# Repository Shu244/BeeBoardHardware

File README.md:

# Overview

This repo contains a generic power supply for ESP32 and other MCUs. This board includes: 

1) Charging circuit with power path
2) Smart power button (for manually/programmtically controlling power)
3) Battery status  

The purpose of this board is to make an MCU portable with precise battery control and monitoring.

## Block Diagram

## Schematic

## PCB

## 3D Models

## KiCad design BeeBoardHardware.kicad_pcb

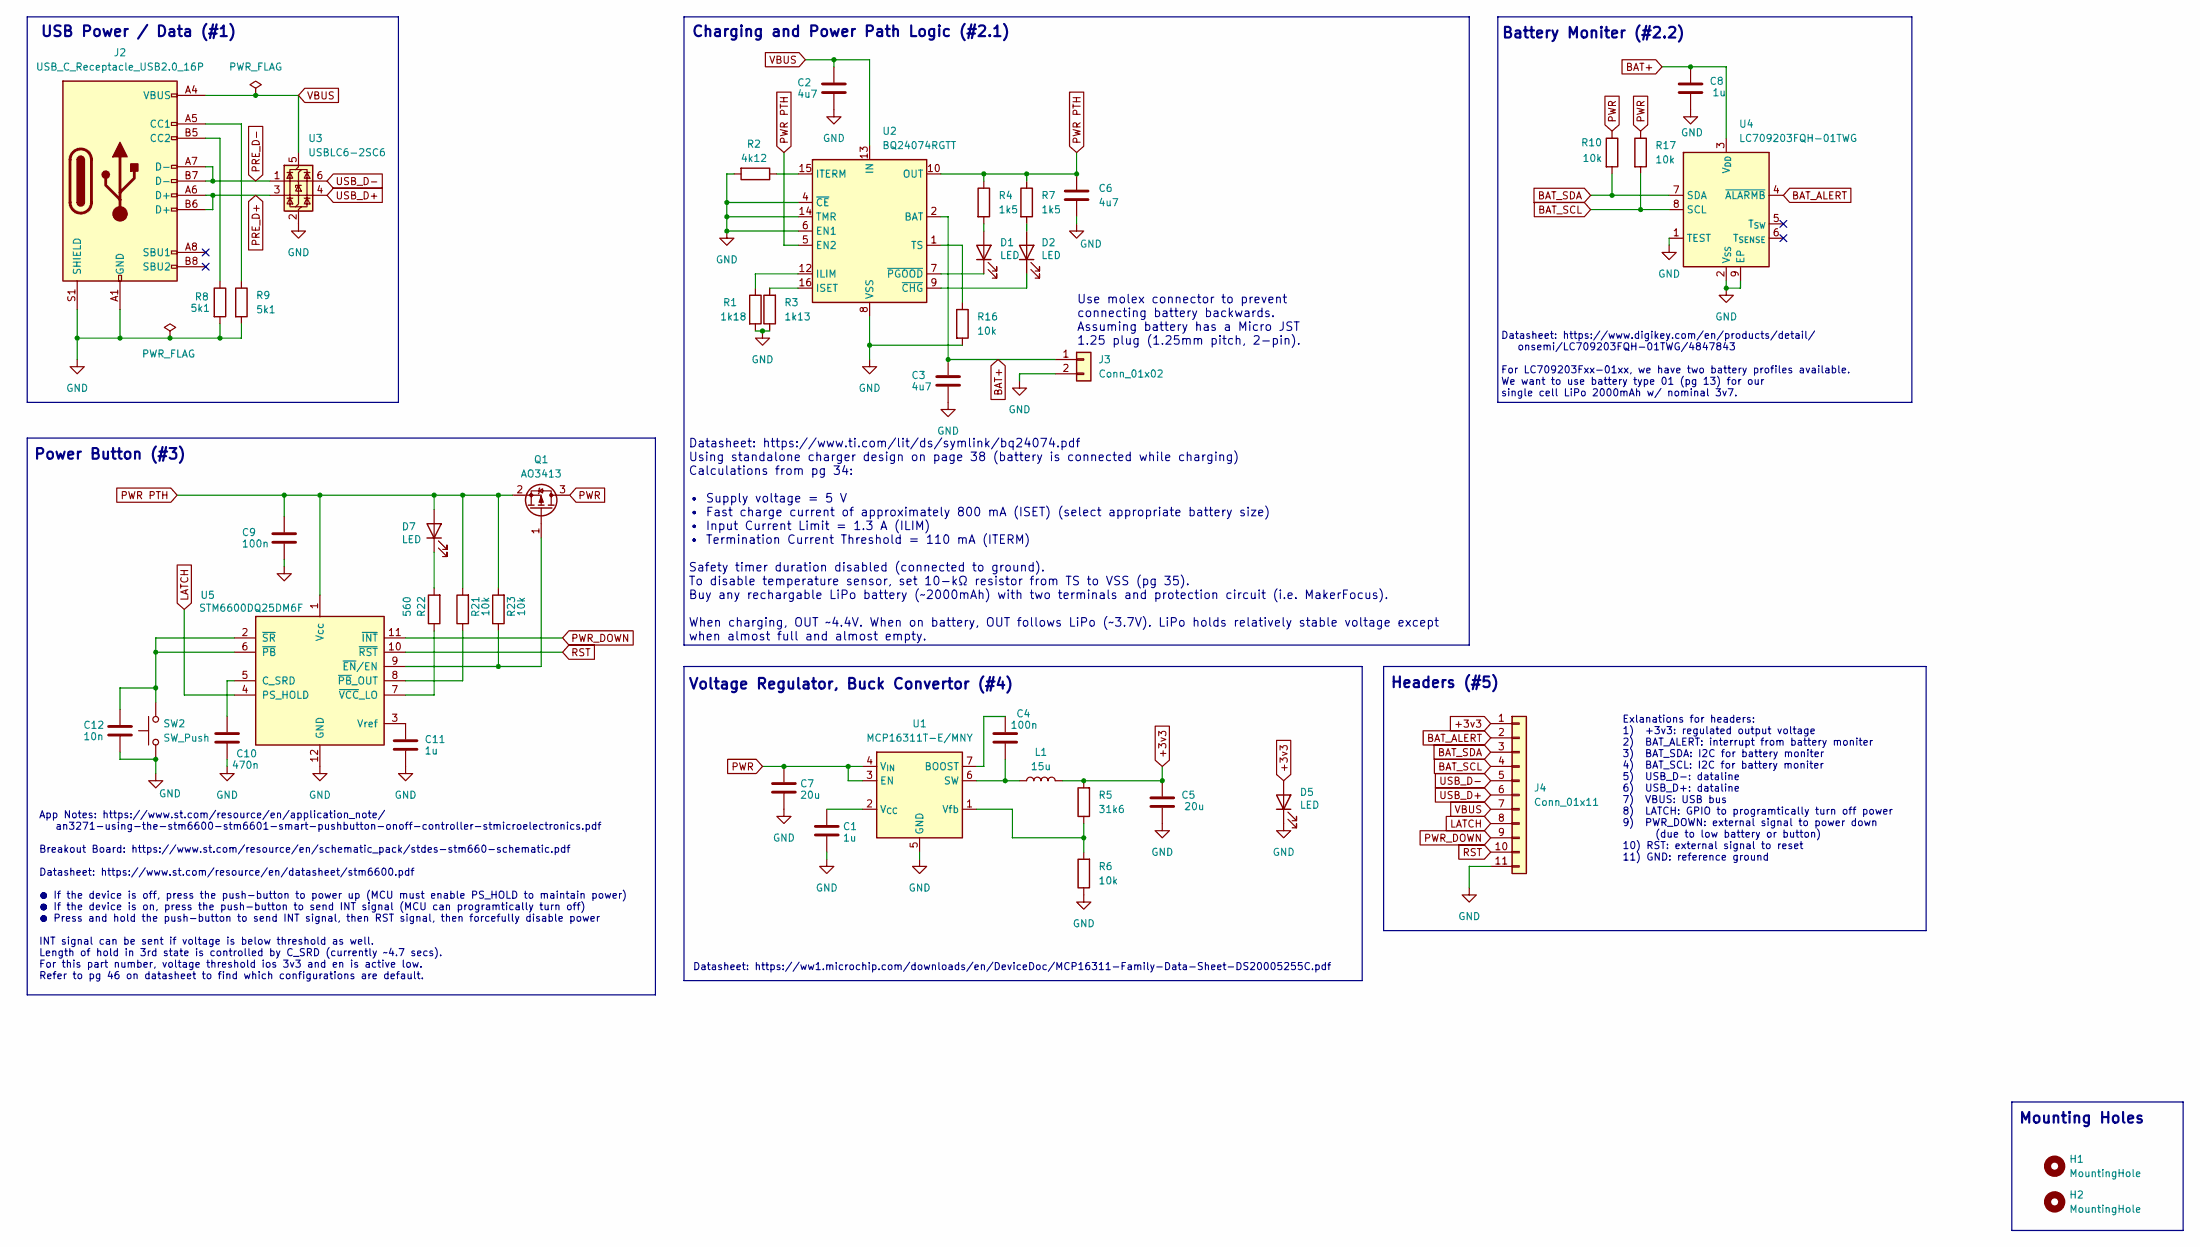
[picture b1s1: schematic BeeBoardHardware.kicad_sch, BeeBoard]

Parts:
C1, C8, C11: 1u; C_0402_1005Metric
C2, C3, C6: 4u7; C_0402_1005Metric
C4, C9: 100n; C_0402_1005Metric
C5, C7: 20u; C_0402_1005Metric
C10: 470n; C_0402_1005Metric
C12: 10n; C_0402_1005Metric
D1, D2, D5, D7: LED; LED_0402_1005Metric
H1, H2: MountingHole; MountingHole_2.1mm
J2: USB_C_Receptacle_USB2.0_16P; USB_C_Receptacle_GCT_USB4105-xx-A_16P_TopMnt_Horizontal
J3: Conn_01x02; JST_GH_BM02B-GHS-TBT_1x02-1MP_P1.25mm_Vertical
J4: Conn_01x11; PinHeader_1x11_P2.54mm_Vertical
L1: 15u; L_0402_1005Metric
Q1: AO3413; SOT-23
R1: 1k18; R_0402_1005Metric
R2: 4k12; R_0402_1005Metric
R3: 1k13; R_0402_1005Metric
R4, R7: 1k5; R_0402_1005Metric
R5: 31k6; R_0402_1005Metric
R6, R10, R16, R17, R21, R23: 10k; R_0402_1005Metric
R8, R9: 5k1; R_0402_1005Metric
R22: 560; R_0402_1005Metric
SW2: SW_Push; 3983_switch
U1: MCP16311T-E/MNY; DFN-8-1EP_3x2mm_P0.5mm_EP1.75x1.45mm
U2: BQ24074RGTT; VQFN-16-1EP_3x3mm_P0.5mm_EP1.6x1.6mm
U3: USBLC6-2SC6; SOT-23-6
U4: LC709203FQH-01TWG; WDFN-8-1EP_4x3mm_P0.65mm_EP2.4x1.8mm
U5: STM6600DQ25DM6F; TDFN-12_2x3mm_P0.5mm

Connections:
+3v3: C5.1, D5.2 (A), J4.1, L1.2, R5.2
BAT+: C3.1, C8.1, J3.1, U2.2 (BAT), U2.3 (BAT), U4.3 (V_{DD})
BAT_ALERT: J4.2, U4.4 (~ALARMB)
BAT_SCL: J4.4, R17.2, U4.8 (SCL)
BAT_SDA: J4.3, R10.2, U4.7 (SDA)
GND: C1.2, C2.2, C3.2, C5.2, C6.2, C7.2, C8.2, C9.2, C10.2, C11.2, C12.2, D5.1 (K), J2.A1 (GND), J2.A12 (GND), J2.B1 (GND), J2.B12 (GND), J2.S1 (SHIELD), J3.2, J4.11, R1.2, R2.2, R3.1, R6.1, R8.2, R9.2, R16.2, SW2.1, U1.5 (GND), U1.8 (GND), U1.9 (GND), U2.4 (~CE), U2.6 (EN1), U2.8 (VSS), U2.14 (TMR), U2.17 (VSS), U3.2 (GND), U4.1 (TEST), U4.2 (V_{SS}), U4.9 (EP), U5.12 (GND)
LATCH: J4.8, U5.4 (PS_HOLD)
unnamed: D1.2 (A), R4.2
unnamed: D1.1 (K), U2.7 (~PGOOD)
unnamed: D2.2 (A), R7.2
unnamed: D2.1 (K), U2.9 (~CHG)
unnamed: D7.1 (K), R22.2
unnamed: J2.A5 (CC1), R9.1
unnamed: J2.B5 (CC2), R8.1
unnamed: Q1.1 (G), R23.1, U5.9 (~EN/EN)
unnamed: C4.2, U1.7 (BOOST)
unnamed: C4.1, L1.1, U1.6 (SW)
unnamed: C1.1, U1.2 (V_{CC})
unnamed: R5.1, R6.2, U1.1 (Vfb)
unnamed: R1.1, U2.12 (ILIM)
unnamed: R3.2, U2.16 (ISET)
unnamed: R2.1, U2.15 (ITERM)
unnamed: R16.1, U2.1 (TS)
unnamed: C10.1, U5.5 (C_SRD)
unnamed: C11.1, U5.3 (Vref)
unnamed: C12.1, SW2.2, U5.2 (~SR), U5.6 (~PB)
unnamed: R21.1, U5.8 (~PB_OUT)
unnamed: R22.1, U5.7 (~VCC_LO)
PRE_D+: J2.A6 (D+), J2.B6 (D+), U3.3 (I/O2)
PRE_D-: J2.A7 (D-), J2.B7 (D-), U3.1 (I/O1)
PWR: C7.1, Q1.3 (D), R10.1, R17.1, U1.3 (EN), U1.4 (V_{IN})
PWR PTH: C6.1, C9.1, D7.2 (A), Q1.2 (S), R4.1, R7.1, R21.2, R23.2, U2.5 (EN2), U2.10 (OUT), U2.11 (OUT), U5.1 (Vcc)
PWR_DOWN: J4.9, U5.11 (~INT)
RST: J4.10, U5.10 (~RST)
USB_D+: J4.6, U3.4 (I/O2)
USB_D-: J4.5, U3.6 (I/O1)
VBUS: C2.1, J2.A4 (VBUS), J2.A9 (VBUS), J2.B4 (VBUS), J2.B9 (VBUS), J4.7, U2.13 (IN), U3.5 (VBUS)

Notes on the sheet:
Use molex connector to prevent connecting battery backwards. Assuming battery has a Micro JST 1.25 plug (1.25mm pitch, 2-pin).
Power Button (#3)
Headers (#5)
Datasheet: https://www.ti.com/lit/ds/symlink/bq24074.pdf Using standalone charger design on page 38 (battery is connected while charging) Calculations from pg 34: • Supply voltage = 5 V • Fast charge current of approximately 800 mA (ISET) (select appropriate battery size) • Input Current Limit = 1.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
Exlanations for headers: 1) +3v3: regulated output voltage 2) BAT_ALERT: interrupt from battery moniter 3) BAT_SDA: I2C for battery moniter 4) BAT_SCL: I2C for battery moniter 5) USB_D-: dataline 6) USB_D+: dataline 7) VBUS: USB bus 8) LATCH: GPIO to programtically turn off power 9) PWR_DOWN: exter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
Mounting Holes
Datasheet: https://ww1.microchip.com/downloads/en/DeviceDoc/MCP16311-Family-Data-Sheet-DS20005255C.pdf
Datasheet: https://www.digikey.com/en/products/detail/ onsemi/LC709203FQH-01TWG/4847843 For LC709203Fxx−01xx, we have two battery profiles available. We want to use battery type 01 (pg 13) for our single cell LiPo 2000mAh w/ nominal 3v7.
USB Power / Data (#1)
Voltage Regulator, Buck Convertor (#4)
App Notes: https://www.st.com/resource/en/application_note/ an3271-using-the-stm6600-stm6601-smart-pushbutton-onoff-controller-stmicroelectronics.pdf Breakout Board: https://www.st.com/resource/en/schematic_pack/stdes-stm660-schematic.pdf Datasheet: https://www.st.com/resource/en/datasheet/stm6600.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
Battery Moniter (#2.2)
Charging and Power Path Logic (#2.1)

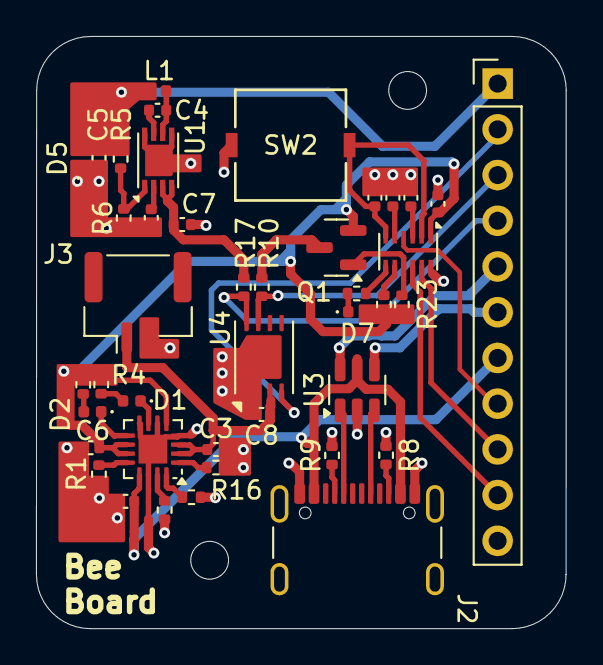
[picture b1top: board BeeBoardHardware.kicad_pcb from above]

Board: 4 copper layers, 29.4 x 32.9 mm, 44 parts (0 on the bottom side), 37 nets.

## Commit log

2025-02-15 schematics
2025-02-15 add readme and updated schematic
2025-02-16 added battery monitor
2025-02-17 updated schematic
2025-02-18 assign footprints
2025-02-18 updated stepper files
2025-02-19 organized pcb
2025-02-21 updated schematics and PCB
2025-02-22 setup all gnd vias and organized parts
2025-02-22 routed more traces
2025-02-22 routing headers next
2025-02-23 finish routes
2025-02-23 clean up silkscreen
2025-02-23 added images
